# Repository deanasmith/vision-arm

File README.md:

# Vision Arm
A robotic arm that mimics the movements of a human's arm using computer vision.

## Getting Started
The project has several components that need to be running:

### Computer Vision
1. Clone the repository
2. Install `uv` by following [their documentation](https://github.com/astral-sh/uv#installation)
3. Run `uv run python main.py <args>`

`<args>` should be any of the following:
- `calibrate`: Calibrate the cameras with the charuco board
- `track` or `stereo`: Start tracking with multiple cameras
- `mono`: Start with a single camera (mostly for debugging). The left shoulder and elbow angles are sent to the STM32 over UART.

`uv run python main.py mono` discovers the USB-UART adapter and opens it at 115200 8N1. On macOS that is the only `/dev/cu.usb*` or `/dev/cu.wchusbserial*` device. If none is listed, mono warns on stderr and keeps the camera running with UART off. On Linux it is the only `/dev/ttyUSB*` device, or `/dev/ttyUSB0` when that listing is empty. If several adapters match, the command prints them and exits. Pass `--port` to choose one:

```
uv run python main.py mono --port /dev/cu.usbserial-10
```

Shoulder is joint id 4 and elbow is joint id 2. If the port cannot be opened, the camera loop still runs and UART stays off.

### STM32
The following STM32 toolchain setup is for Linux systems. A Linux system is recommended, but MacOS or Windows systems should work with some tinkering. (WSL is useful for Windows systems.)
1. Install the following packages (for a Debian-based system):
    - `gcc-arm-none-eabi`
    - `binutils-arm-none-eabi`
    - `cmake`
    - `make`
    - `openocd`
2. Navigate to the `stm32` directory
3. Create the build directory with `cmake -B build -S .`
4. Compile the microcontroller code with `cmake --build build` (this can be skipped if you also want to flash the STM32)
5. Flash the microcontroller with `cmake --build build --target flash`.

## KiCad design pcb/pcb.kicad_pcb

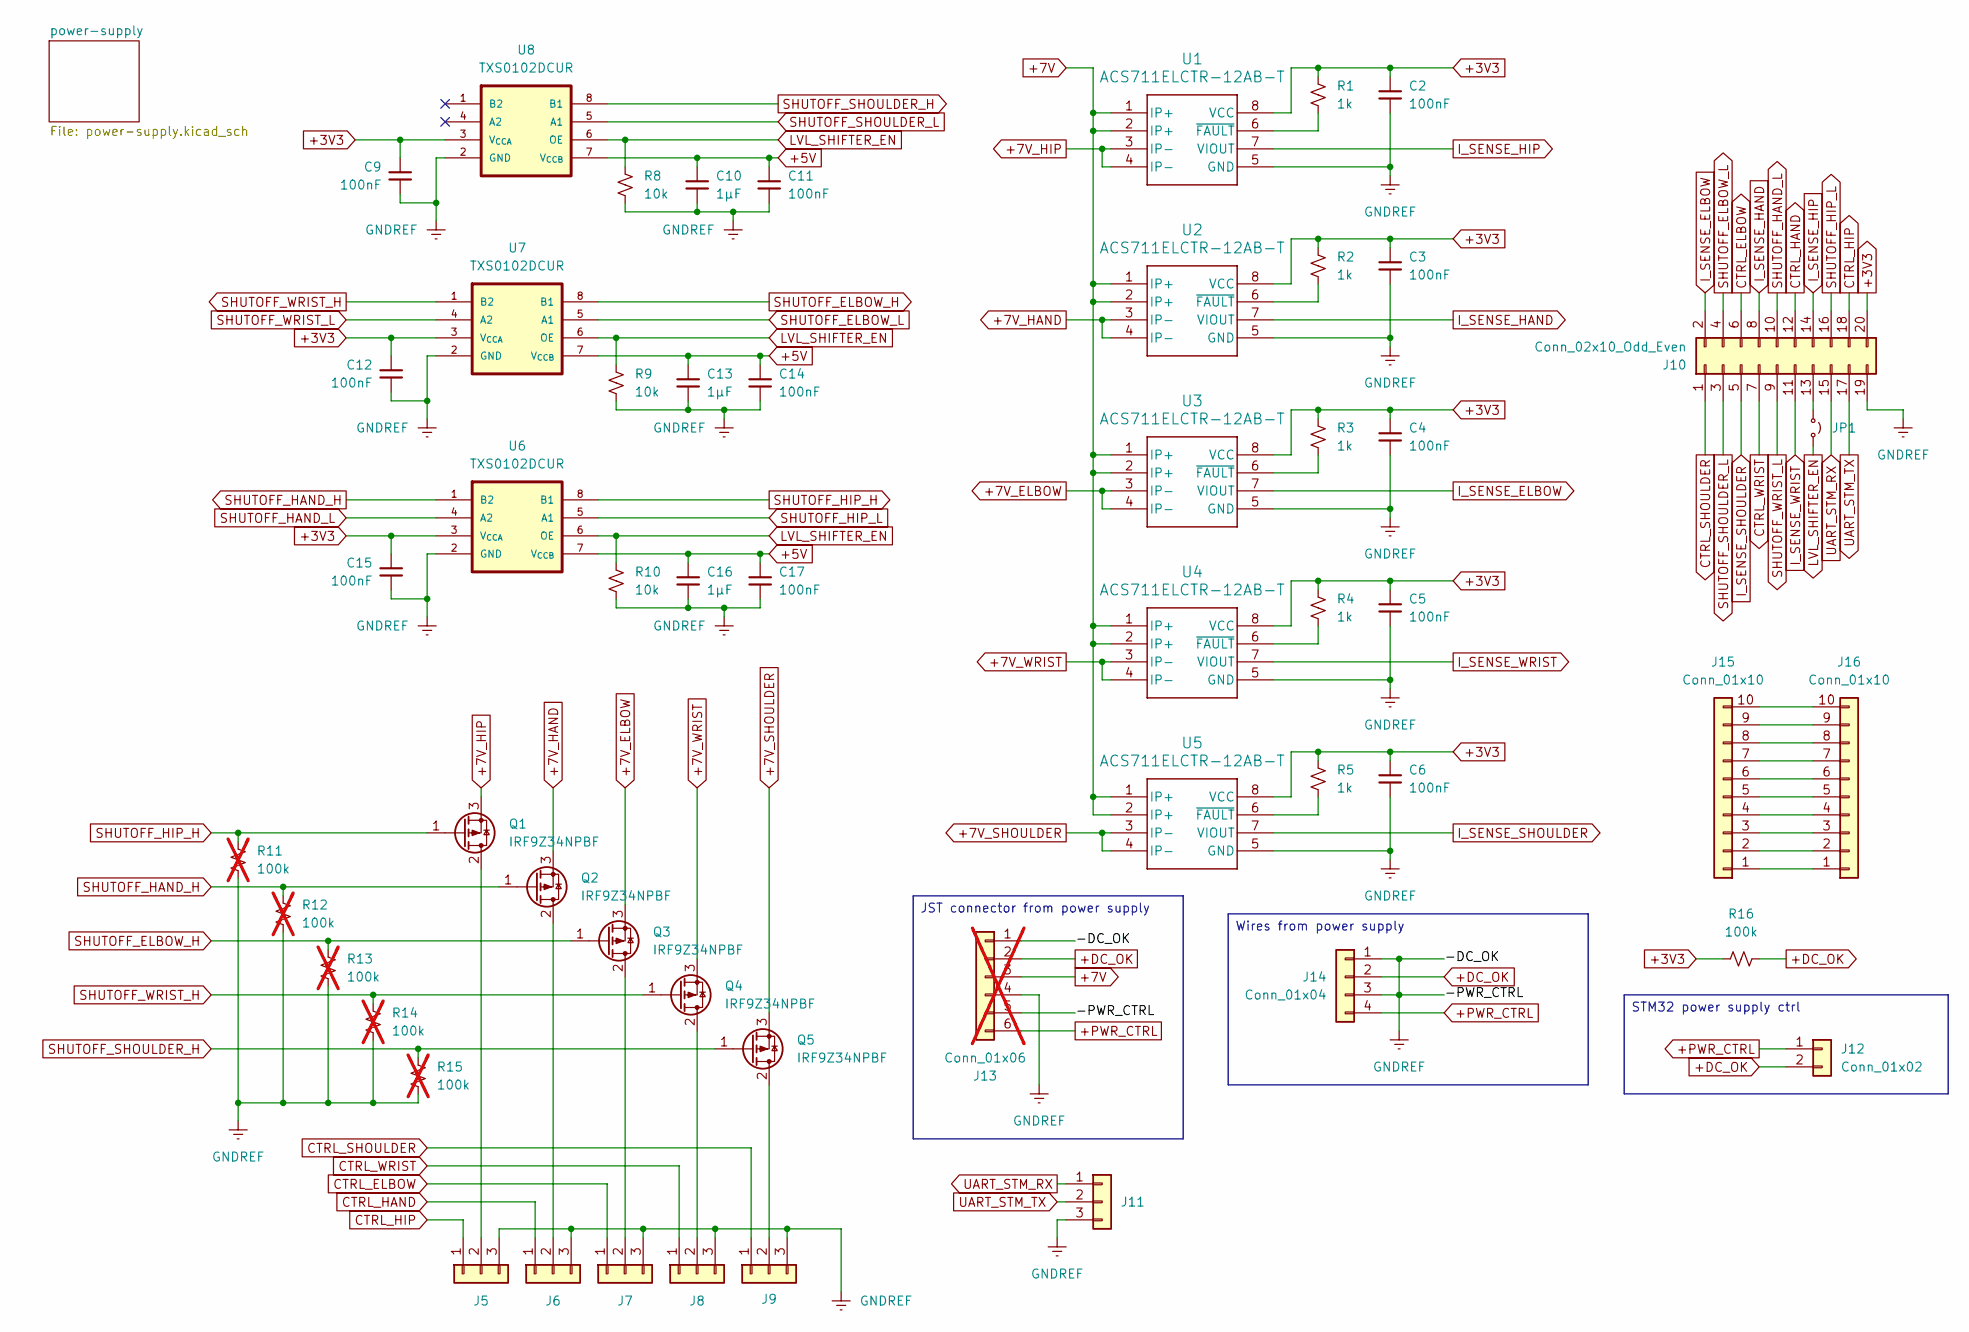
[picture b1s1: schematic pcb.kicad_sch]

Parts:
C2, C3, C4, C5, C6, C9, C11, C12, C14, C15, C17: 100nF; C_0805_2012Metric_Pad1.18x1.45mm_HandSolder
C10, C13, C16: 1µF; C_0805_2012Metric_Pad1.18x1.45mm_HandSolder
J5, J6, J7, J8, J9, J11: Conn_01x03; PinHeader_1x03_P2.54mm_Vertical
J10: Conn_02x10_Odd_Even; PinHeader_2x10_P2.54mm_Vertical
J12: Conn_01x02; PinHeader_1x02_P2.54mm_Vertical
J13: Conn_01x06; LTC-4627Jx; not fitted
J14: Conn_01x04; PinHeader_1x04_P2.54mm_Vertical
J15, J16: Conn_01x10; PinHeader_1x10_P2.54mm_Vertical
JP1: Jumper_2_Small_Open; PinHeader_1x02_P2.54mm_Vertical
Q1, Q2, Q3, Q4, Q5: IRF9Z34NPBF; TO-220-3_Vertical; DigiKey Part Number IRF9Z34NPBF-ND
R1, R2, R3, R4, R5: 1k; R_0805_2012Metric_Pad1.20x1.40mm_HandSolder
R8, R9, R10: 10k; R_0805_2012Metric_Pad1.20x1.40mm_HandSolder
R11, R12, R13, R14, R15: 100k; R_0805_2012Metric_Pad1.20x1.40mm_HandSolder; not fitted
R16: 100k; R_0805_2012Metric_Pad1.20x1.40mm_HandSolder
U1, U2, U3, U4, U5: ACS711ELCTR-12AB-T; SOICN-8_ALM; DigiKey Part Number 620-1370-1-ND
U6, U7, U8: TXS0102DCUR; SOP50P310X90-8N; DigiKey Part Number 296-21931-1-ND

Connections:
+3V3: C2.1, C3.1, C4.1, C5.1, C6.1, C9.1, C12.1, C15.1, J10.20, R1.1, R2.1, R3.1, R4.1, R5.1, R16.2, U1.8 (VCC), U2.8 (VCC), U3.8 (VCC), U4.8 (VCC), U5.8 (VCC), U6.3 (V_{CCA}), U7.3 (V_{CCA}), U8.3 (V_{CCA}); also elsewhere on the board
+5V: C10.1, C11.1, C13.1, C14.1, C16.1, C17.1, U6.7 (V_{CCB}), U7.7 (V_{CCB}), U8.7 (V_{CCB}); also elsewhere on the board
+7V: J13.3, U1.1 (IP+), U1.2 (IP+), U2.1 (IP+), U2.2 (IP+), U3.1 (IP+), U3.2 (IP+), U4.1 (IP+), U4.2 (IP+), U5.1 (IP+), U5.2 (IP+); also elsewhere on the board
+7V_ELBOW: Q3.3 (S), U3.3 (IP-), U3.4 (IP-)
+7V_HAND: Q2.3 (S), U2.3 (IP-), U2.4 (IP-)
+7V_HIP: Q1.3 (S), U1.3 (IP-), U1.4 (IP-)
+7V_SHOULDER: Q5.3 (S), U5.3 (IP-), U5.4 (IP-)
+7V_WRIST: Q4.3 (S), U4.3 (IP-), U4.4 (IP-)
+DC_OK: J12.2, J13.2, J14.2, R16.1
+PWR_CTRL: J12.1, J13.6, J14.4
CTRL_ELBOW: J7.1, J10.6
CTRL_HAND: J6.1, J10.12
CTRL_HIP: J5.1, J10.18
CTRL_SHOULDER: J9.1, J10.1
CTRL_WRIST: J8.1, J10.7
GNDREF: C2.2, C3.2, C4.2, C5.2, C6.2, C9.2, C10.2, C11.2, C12.2, C13.2, C14.2, C15.2, C16.2, C17.2, J5.3, J6.3, J7.3, J8.3, J9.3, J10.19, J11.3, J13.1, J13.4, J13.5, J14.1, J14.3, R8.2, R9.2, R10.2, R11.2, R12.2, R13.2, R14.2, R15.2, U1.5 (GND), U2.5 (GND), U3.5 (GND), U4.5 (GND), U5.5 (GND), U6.2 (GND), U7.2 (GND), U8.2 (GND); also elsewhere on the board
I_SENSE_ELBOW: J10.2, U3.7 (VIOUT)
I_SENSE_HAND: J10.8, U2.7 (VIOUT)
I_SENSE_HIP: J10.14, U1.7 (VIOUT)
I_SENSE_SHOULDER: J10.5, U5.7 (VIOUT)
I_SENSE_WRIST: J10.11, U4.7 (VIOUT)
LVL_SHIFTER_EN: JP1.2 (B), R8.1, R9.1, R10.1, U6.6 (OE), U7.6 (OE), U8.6 (OE)
unnamed: J5.2, Q1.2 (D)
unnamed: J6.2, Q2.2 (D)
unnamed: J7.2, Q3.2 (D)
unnamed: J8.2, Q4.2 (D)
unnamed: J9.2, Q5.2 (D)
unnamed: J10.13, JP1.1 (A)
unnamed: J15.1, J16.1
unnamed: J15.2, J16.2
unnamed: J15.3, J16.3
unnamed: J15.4, J16.4
unnamed: J15.5, J16.5
unnamed: J15.6, J16.6
unnamed: J15.7, J16.7
unnamed: J15.8, J16.8
unnamed: J15.9, J16.9
unnamed: J15.10, J16.10
unnamed: R1.2, U1.6 (~FAULT)
unnamed: R2.2, U2.6 (~FAULT)
unnamed: R3.2, U3.6 (~FAULT)
unnamed: R4.2, U4.6 (~FAULT)
unnamed: R5.2, U5.6 (~FAULT)
SHUTOFF_ELBOW_H: Q3.1 (G), R13.1, U7.8 (B1)
SHUTOFF_ELBOW_L: J10.4, U7.5 (A1)
SHUTOFF_HAND_H: Q2.1 (G), R12.1, U6.1 (B2)
SHUTOFF_HAND_L: J10.10, U6.4 (A2)
SHUTOFF_HIP_H: Q1.1 (G), R11.1, U6.8 (B1)
SHUTOFF_HIP_L: J10.16, U6.5 (A1)
SHUTOFF_SHOULDER_H: Q5.1 (G), R15.1, U8.8 (B1)
SHUTOFF_SHOULDER_L: J10.3, U8.5 (A1)
SHUTOFF_WRIST_H: Q4.1 (G), R14.1, U7.1 (B2)
SHUTOFF_WRIST_L: J10.9, U7.4 (A2)
UART_STM_RX: J10.15, J11.1
UART_STM_TX: J10.17, J11.2

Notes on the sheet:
JST connector from power supply
Wires from power supply
STM32 power supply ctrl

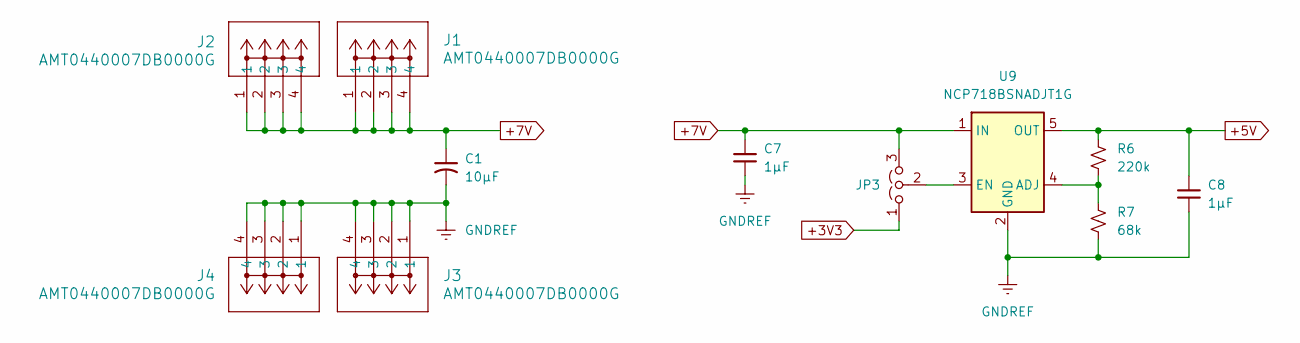
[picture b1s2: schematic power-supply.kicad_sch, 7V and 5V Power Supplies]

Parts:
C1: 10µF; C_Radial_D6.3mm_H11.0mm_P2.50mm
C7, C8: 1µF; C_0805_2012Metric_Pad1.18x1.45mm_HandSolder
J1, J2, J3, J4: AMT0440007DB0000G; CONN_AMT0440007DB0000G_AMP; Mouser Part Number 523-AMT0680001DB000G; DigiKey Part Number 1818-AMT0440007DB0000G-ND
JP3: Jumper_3_Open; PinHeader_1x03_P2.54mm_Vertical
R6: 220k; R_0805_2012Metric_Pad1.20x1.40mm_HandSolder
R7: 68k; R_0805_2012Metric_Pad1.20x1.40mm_HandSolder
U9: NCP718BSNADJT1G; TSOT-23-5_HandSoldering; DigiKey Part Number NCP718BSNADJT1GOSCT-ND

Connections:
+3V3: JP3.1 (A); also elsewhere on the board
+5V: C8.1, R6.1, U9.5 (OUT); also elsewhere on the board
+7V: C1.1, C7.1, J1.1, J1.2, J1.3, J1.4, J2.1, J2.2, J2.3, J2.4, JP3.3 (B), U9.1 (IN); also elsewhere on the board
GNDREF: C1.2, C7.2, C8.2, J3.1, J3.2, J3.3, J3.4, J4.1, J4.2, J4.3, J4.4, R7.2, U9.2 (GND); also elsewhere on the board
unnamed: JP3.2 (C), U9.3 (EN)
unnamed: R6.2, R7.1, U9.4 (ADJ)

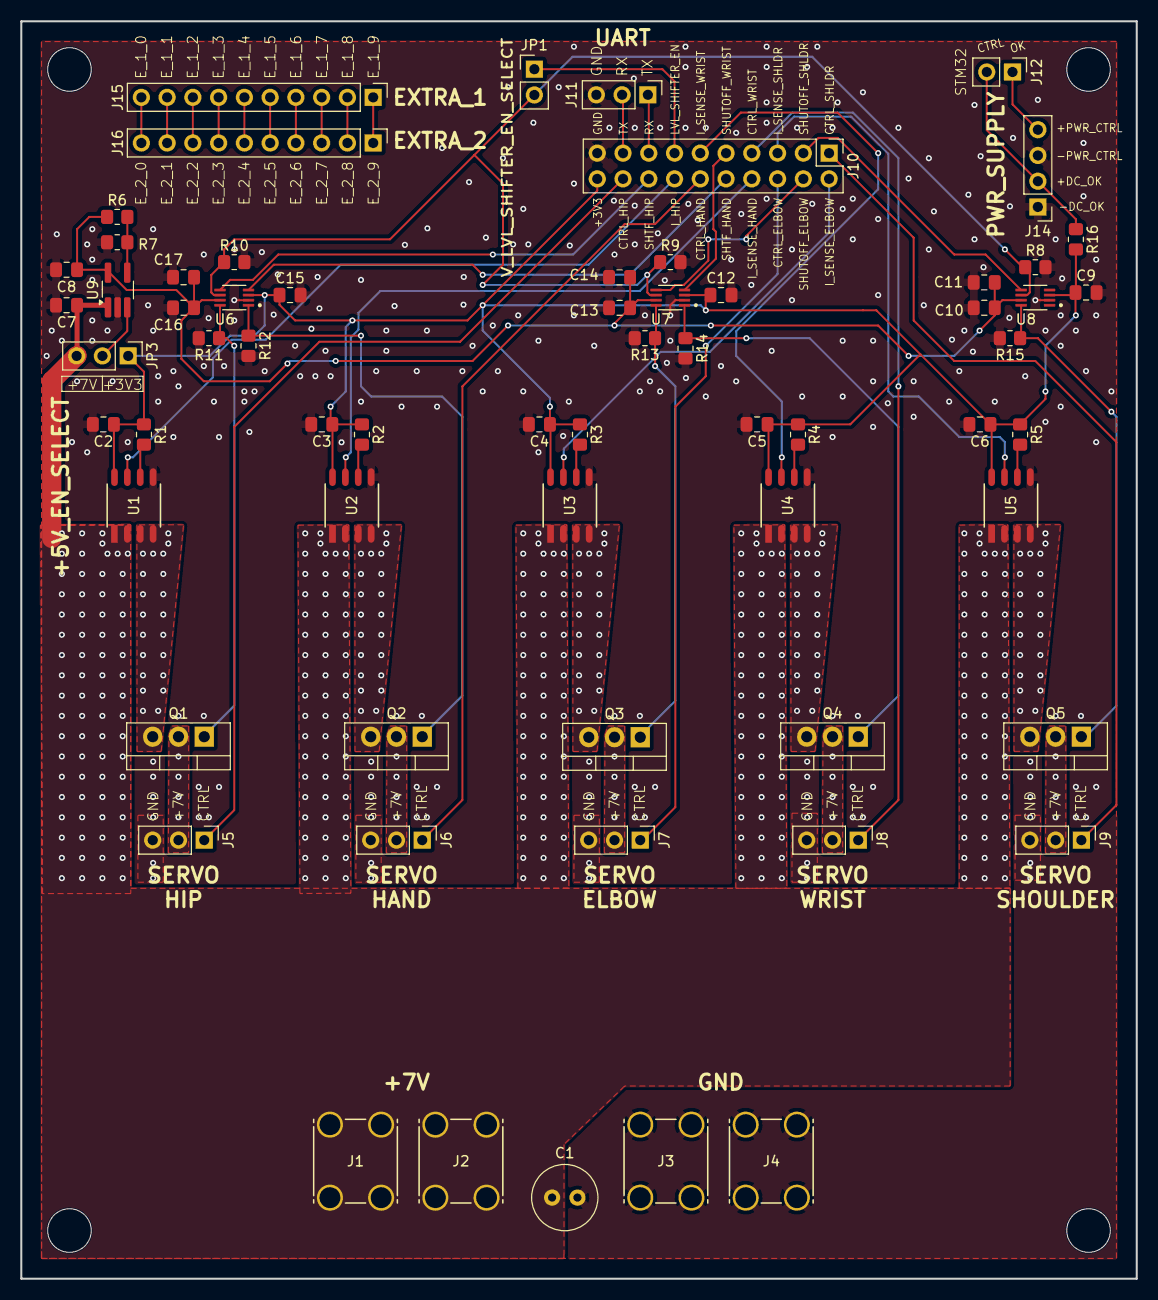
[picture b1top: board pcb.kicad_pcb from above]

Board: 2 copper layers, 110.0 x 124.0 mm, 64 parts (0 on the bottom side), 57 nets.
